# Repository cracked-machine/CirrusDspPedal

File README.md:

CirrusDspPedal

Required Kicad Hardware library: https://github.com/cracked-machine/KicadLibrary

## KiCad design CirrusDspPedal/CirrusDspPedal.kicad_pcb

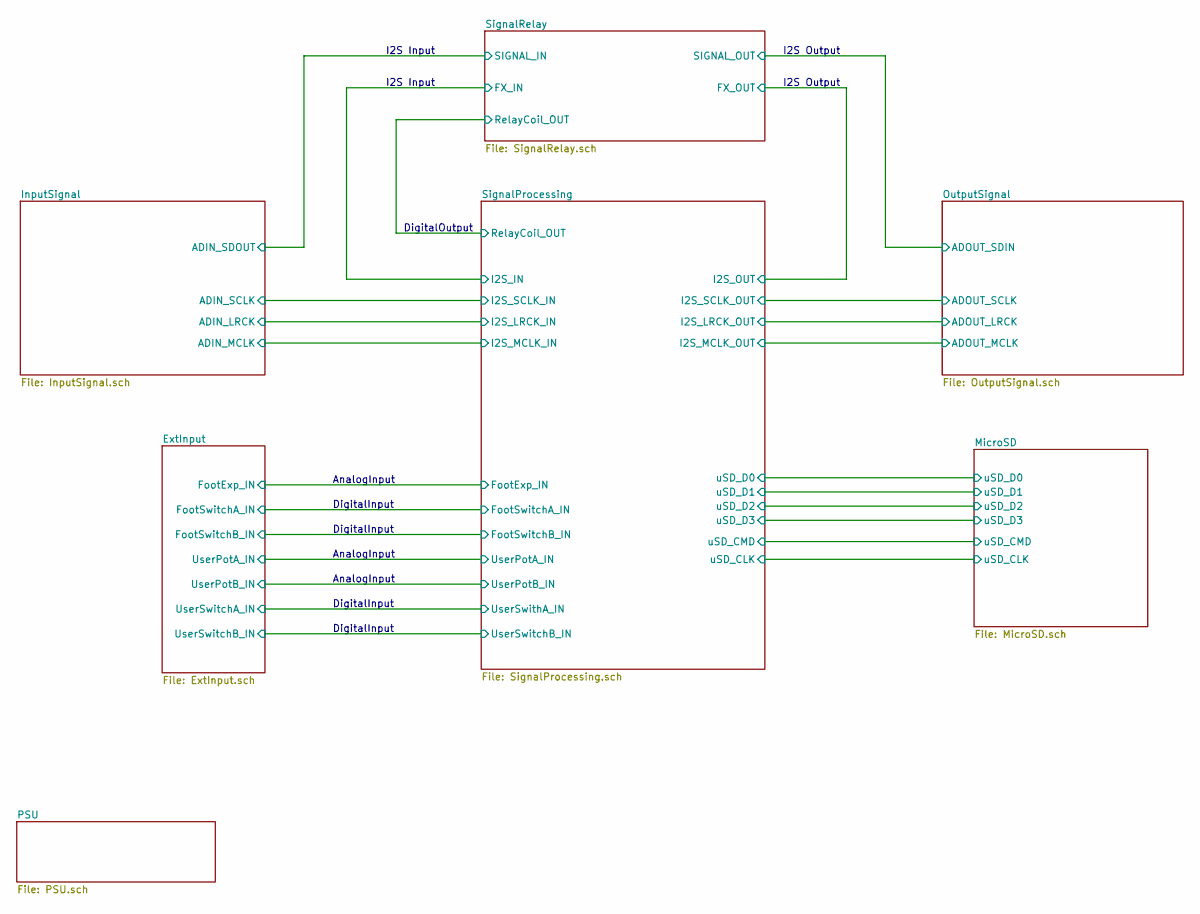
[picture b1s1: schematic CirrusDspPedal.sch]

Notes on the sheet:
AnalogInput
DigitalInput
DigitalOutput
I2S Input
I2S Output

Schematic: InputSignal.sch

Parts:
C1, C6: 100nF; C_0805_2012Metric_Pad1.15x1.40mm_HandSolder
C2, C4: 1uF; C_0805_2012Metric_Pad1.15x1.40mm_HandSolder
C3: 10uF; C_0805_2012Metric_Pad1.15x1.40mm_HandSolder
C5: 180pF C0G; C_0805_2012Metric_Pad1.15x1.40mm_HandSolder
C25, C26, C32: 1uF; C_0805_2012Metric_Pad1.18x1.45mm_HandSolder
C27, C34, C35: 100nF; C_0805_2012Metric_Pad1.18x1.45mm_HandSolder
C31: 270pF; C_0805_2012Metric_Pad1.18x1.45mm_HandSolder
D3: LED; LED_0805_2012Metric_Pad1.15x1.40mm_HandSolder
J1: MonoJack2Switch; NRJxHx_NOTAB
R1, R2: 5K1; R_0805_2012Metric_Pad1.15x1.40mm_HandSolder
R3: 10K; R_0805_2012Metric_Pad1.15x1.40mm_HandSolder
R13: 2K2; R_0805_2012Metric_Pad1.20x1.40mm_HandSolder
R14: 47R; R_0805_2012Metric_Pad1.20x1.40mm_HandSolder
R30: 100K; R_0805_2012Metric_Pad1.20x1.40mm_HandSolder
RV1: 100K; Potentiometer_Bourns_3314J_Vertical
U1: CS5343; TSSOP-10_3x3mm_P0.5mm
U2: 74AHC1G126; SOT-23-5_HandSoldering
U8: TPS60400; SOT-23-5_HandSoldering
U9: OPA197IDBV; SOT-23-5

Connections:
/InputSignal/ADIN_LRCK: U1.3 (LRCK); also elsewhere on the board
/InputSignal/ADIN_MCLK: U1.4 (MCLK); also elsewhere on the board
/InputSignal/ADIN_SCLK: U1.2 (SCLK); also elsewhere on the board
/InputSignal/ADIN_SDOUT: R3.1, U2.4; also elsewhere on the board
/InputSignal/FILT: C3.1, U1.5 (FILT)
/InputSignal/SDOUT: U1.1 (SDOUT), U2.2
/InputSignal/VA: U1.10 (VA); also elsewhere on the board
/InputSignal/VQ: C1.1, C2.1, U1.7 (VQ)
unnamed: C4.1, C5.2, U1.6 (AINL)
unnamed: C4.2, R1.1, R2.2
unnamed: C25.1, U8.3 (CFLY-)
unnamed: C25.2, U8.5 (CFLY+)
unnamed: C26.1, D3.1, R14.2, U8.1 (OUT)
unnamed: D3.2, R13.2
unnamed: J1.1 (TIP), U9.3 (+)

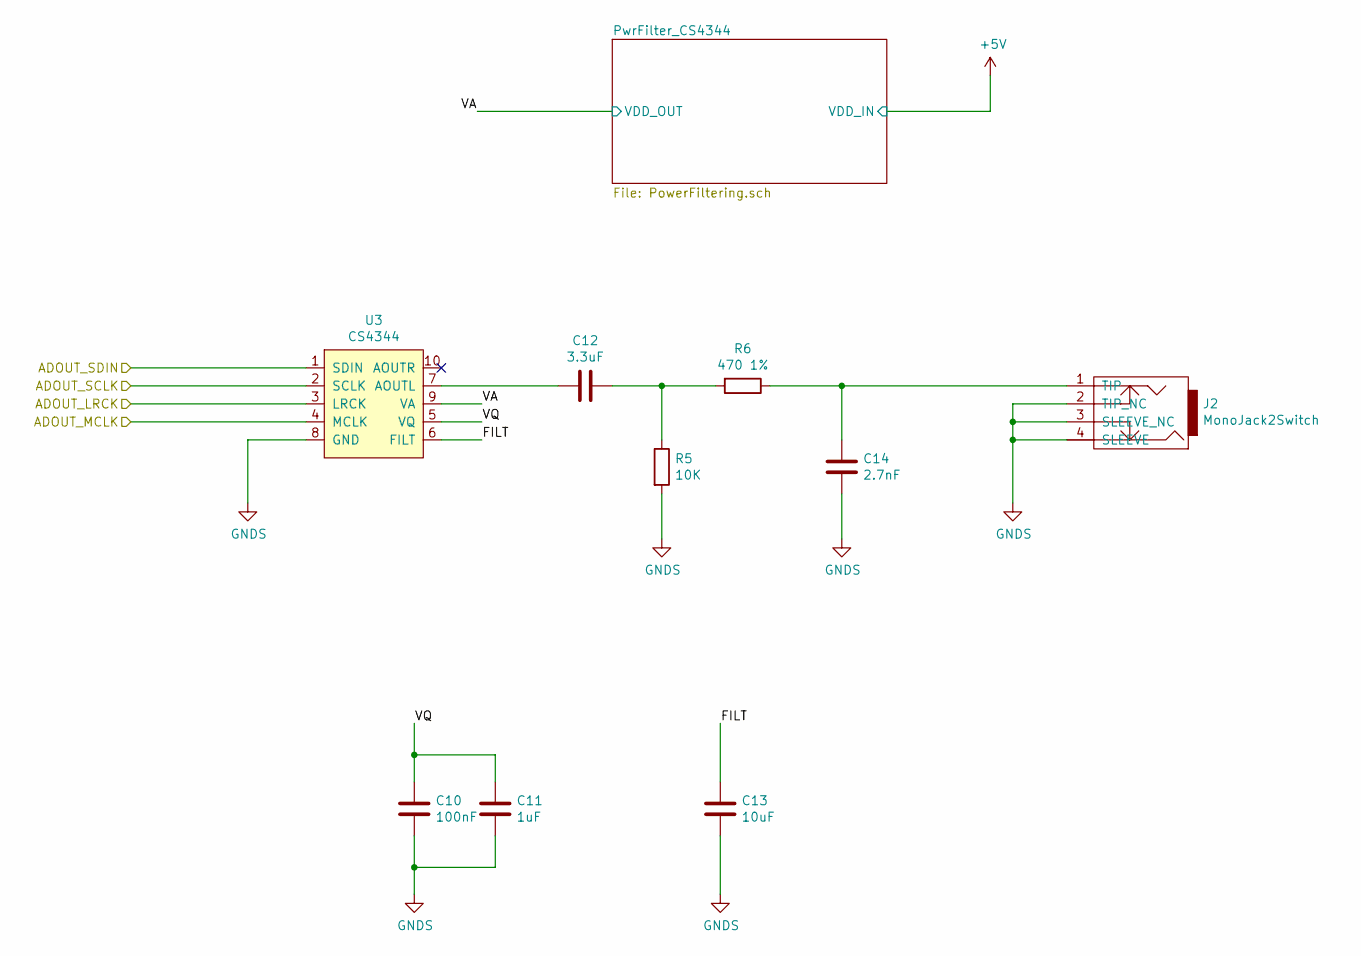
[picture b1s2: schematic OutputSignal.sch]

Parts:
C10: 100nF; C_0805_2012Metric_Pad1.15x1.40mm_HandSolder
C11: 1uF; C_0805_2012Metric_Pad1.15x1.40mm_HandSolder
C12: 3.3uF; C_0805_2012Metric_Pad1.15x1.40mm_HandSolder
C13: 10uF; C_0805_2012Metric_Pad1.15x1.40mm_HandSolder
C14: 2.7nF; C_0805_2012Metric_Pad1.15x1.40mm_HandSolder
J2: MonoJack2Switch; NRJxHx_NOTAB
R5: 10K; R_0805_2012Metric_Pad1.15x1.40mm_HandSolder
R6: 470 1%; R_0805_2012Metric_Pad1.15x1.40mm_HandSolder
U3: CS4344; TSSOP-10_3x3mm_P0.5mm

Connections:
/InputSignal/ADIN_LRCK: U3.3 (LRCK); also elsewhere on the board
/InputSignal/ADIN_MCLK: U3.4 (MCLK); also elsewhere on the board
/InputSignal/ADIN_SCLK: U3.2 (SCLK); also elsewhere on the board
/OutputSignal/ADOUT_SDIN: U3.1 (SDIN); also elsewhere on the board
/OutputSignal/FILT: C13.1, U3.6 (FILT)
/OutputSignal/VA: U3.9 (VA); also elsewhere on the board
/OutputSignal/VQ: C10.1, C11.1, U3.5 (VQ)
unnamed: C12.1, R5.1, R6.2
unnamed: C12.2, U3.7 (AOUTL)
unnamed: C14.2, J2.1 (TIP), R6.1

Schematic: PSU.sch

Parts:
C23, C24, C28, C29: 1uF; C_1206_3216Metric_Pad1.42x1.75mm_HandSolder
D1: D_Schottky; D_SOD-123F
J4: Barrel_Jack_Switch; BarrelJack_Horizontal
J7: Conn_01x01; TestPoint_Pad_2.0x2.0mm
U4: SE8250X2_SOT23; SOT-23
U5: MCP1703A-1202_SOT223; SOT-223-3_TabPin2

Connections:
+3V3: C29.1, U5.3 (VO); also elsewhere on the board
GNDPWR: J7.1; also elsewhere on the board
unnamed: C23.1, C28.1, D1.1 (K), U4.3, U5.1 (VI)
unnamed: D1.2 (A), J4.2

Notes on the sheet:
Center Negative!
16Vin Max 250mA out
30Vin Max 100mA out

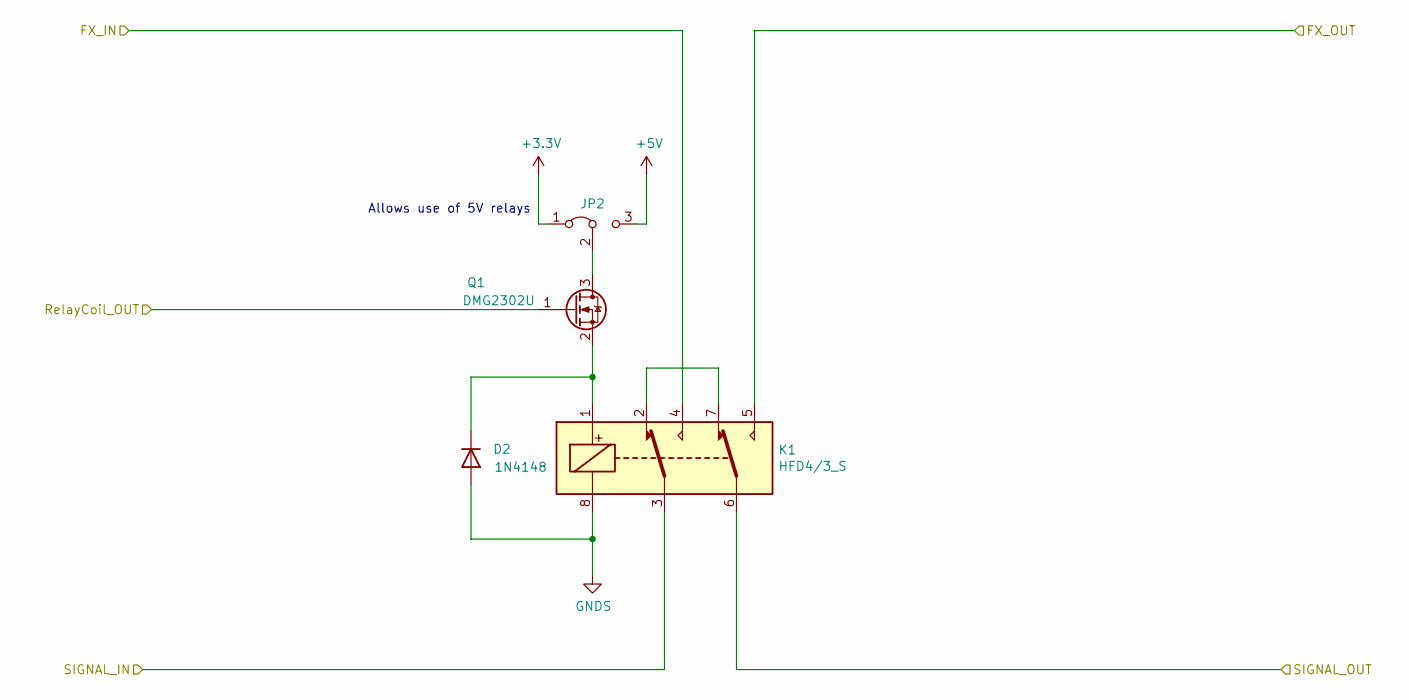
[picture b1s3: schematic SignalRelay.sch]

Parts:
D2: 1N4148; D_SOD-123F
JP2: Jumper_3_Bridged12; SolderJumper-3_P1.3mm_Bridged2Bar12_Pad1.0x1.5mm
K1: HFD4/3_S; Relay_Fujitsu_FTR-B3S
Q1: DMG2302U; SOT-23

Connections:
+3V3: JP2.1 (A); also elsewhere on the board
/InputSignal/ADIN_SDOUT: K1.3; also elsewhere on the board
/OutputSignal/ADOUT_SDIN: K1.6; also elsewhere on the board
/SignalProcessing/RelayCoil_OUT: Q1.1 (G); also elsewhere on the board
/SignalRelay/FX_IN: K1.4; also elsewhere on the board
/SignalRelay/FX_OUT: K1.5; also elsewhere on the board
unnamed: D2.1 (K), K1.1, Q1.2 (S)
unnamed: JP2.2 (C), Q1.3 (D)
unnamed: K1.2, K1.7

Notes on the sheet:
Allows use of 5V relays

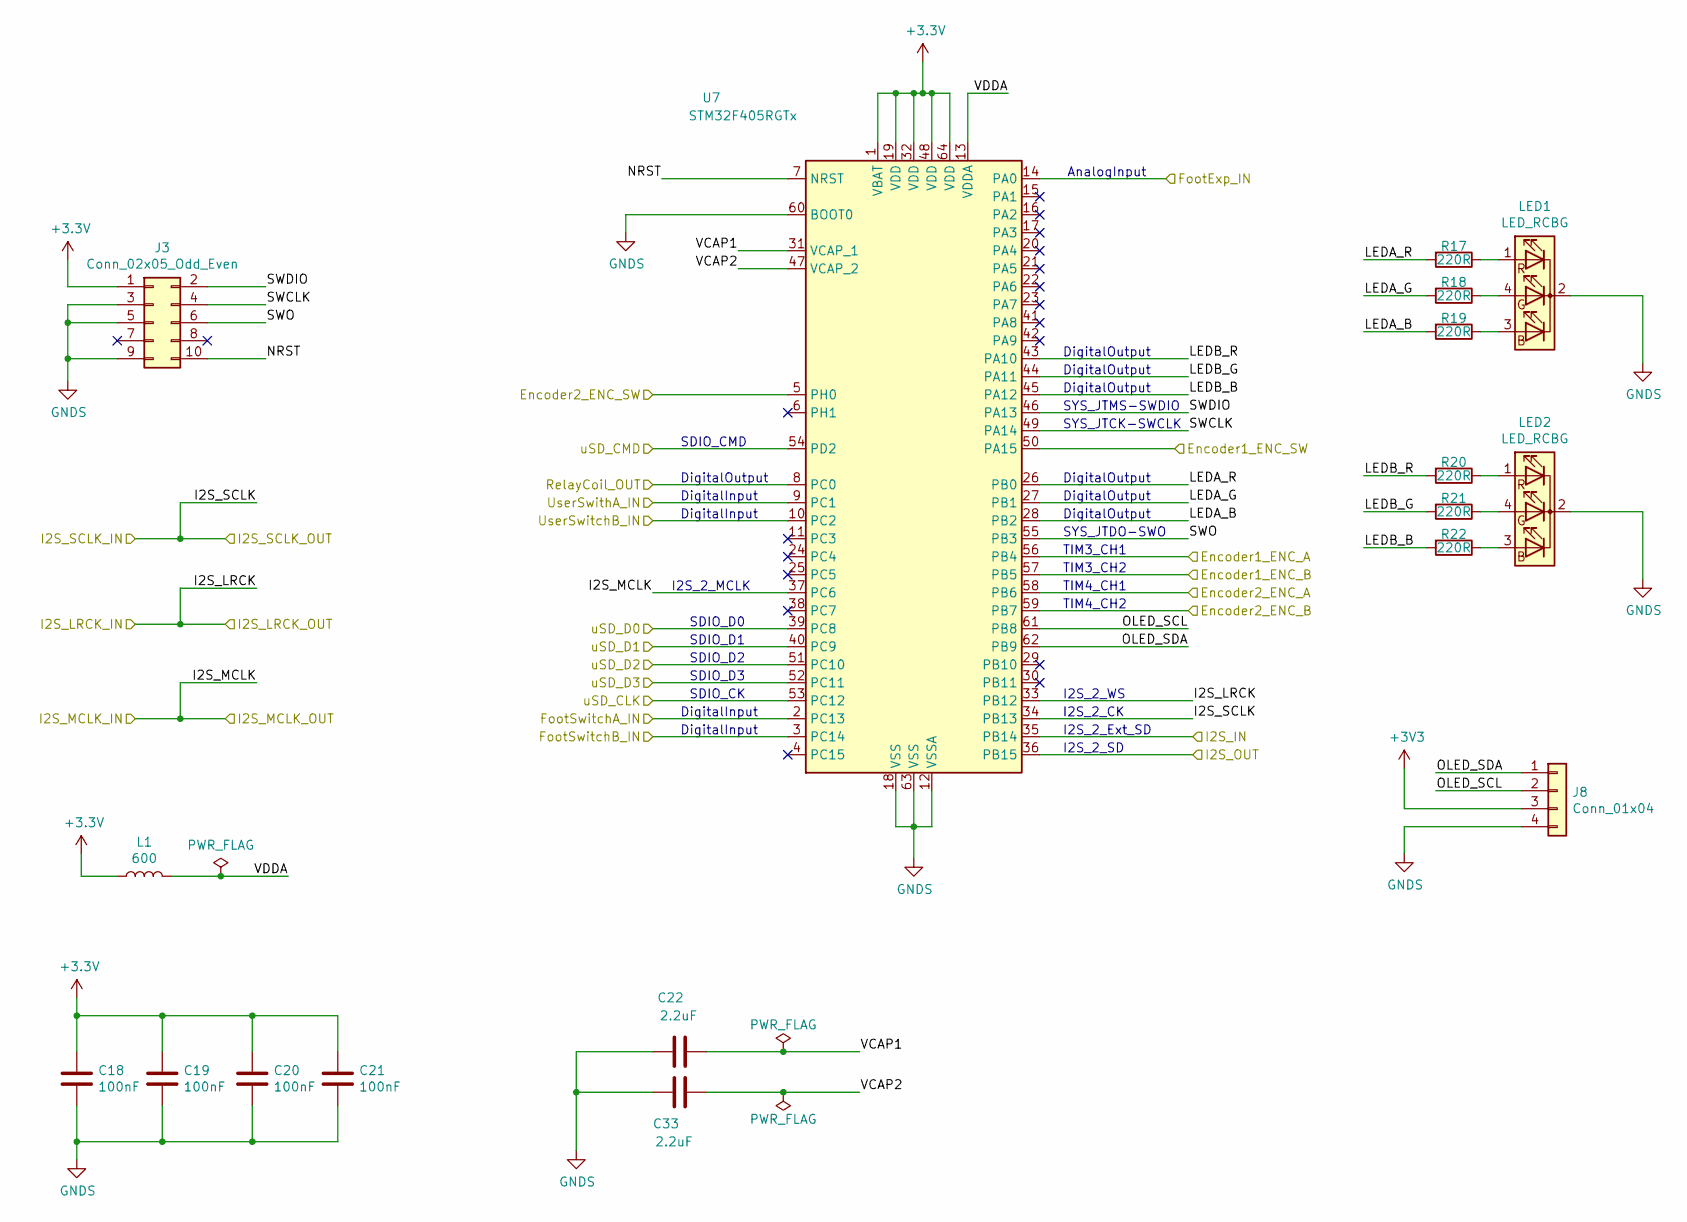
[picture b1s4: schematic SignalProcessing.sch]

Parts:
C18, C19, C20, C21: 100nF; C_0805_2012Metric_Pad1.15x1.40mm_HandSolder
C22, C33: 2.2uF; C_0805_2012Metric_Pad1.15x1.40mm_HandSolder
J3: Conn_02x05_Odd_Even; PinHeader_2x05_P1.27mm_Vertical_SMD
J8: Conn_01x04; Molex_KK-254_AE-6410-04A_1x04_P2.54mm_Vertical
L1: 600; L_0805_2012Metric_Pad1.15x1.40mm_HandSolder
LED1, LED2: LED_RCBG; LED_D5.0mm-4_RGB_Wide_Pins
R17, R18, R19, R20, R21, R22: 220R; R_0805_2012Metric_Pad1.15x1.40mm_HandSolder
U7: STM32F405RGTx; LQFP-64_10x10mm_P0.5mm

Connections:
+3V3: C18.1, C19.1, C20.1, C21.1, J3.1, L1.1, U7.1 (VBAT), U7.19 (VDD), U7.32 (VDD), U7.48 (VDD), U7.64 (VDD); also elsewhere on the board
/ExtInput/Encoder1_ENC_A: U7.56 (PB4); also elsewhere on the board
/ExtInput/Encoder1_ENC_B: U7.57 (PB5); also elsewhere on the board
/ExtInput/Encoder1_ENC_SW: U7.50 (PA15); also elsewhere on the board
/ExtInput/Encoder2_ENC_SW: U7.5 (PH0); also elsewhere on the board
/ExtInput/FootExp_IN: U7.14 (PA0); also elsewhere on the board
/ExtInput/FootSwitchA_IN: U7.2 (PC13); also elsewhere on the board
/ExtInput/FootSwitchB_IN: U7.3 (PC14); also elsewhere on the board
/ExtInput/UserSwitchA_IN: U7.9 (PC1); also elsewhere on the board
/ExtInput/UserSwitchB_IN: U7.10 (PC2); also elsewhere on the board
/InputSignal/ADIN_LRCK: U7.33 (PB12); also elsewhere on the board
/InputSignal/ADIN_MCLK: U7.37 (PC6); also elsewhere on the board
/InputSignal/ADIN_SCLK: U7.34 (PB13); also elsewhere on the board
/MicroSD/uSD_CLK: U7.53 (PC12); also elsewhere on the board
/MicroSD/uSD_CMD: U7.54 (PD2); also elsewhere on the board
/MicroSD/uSD_D0: U7.39 (PC8); also elsewhere on the board
/MicroSD/uSD_D1: U7.40 (PC9); also elsewhere on the board
/MicroSD/uSD_D2: U7.51 (PC10); also elsewhere on the board
/MicroSD/uSD_D3: U7.52 (PC11); also elsewhere on the board
/SignalProcessing/LEDA_B: R19.2, U7.28 (PB2)
/SignalProcessing/LEDA_G: R18.2, U7.27 (PB1)
/SignalProcessing/LEDA_R: R17.2, U7.26 (PB0)
/SignalProcessing/LEDB_B: R22.2, U7.45 (PA12)
/SignalProcessing/LEDB_G: R21.2, U7.44 (PA11)
/SignalProcessing/LEDB_R: R20.2, U7.43 (PA10)
/SignalProcessing/NRST: J3.10, U7.7 (NRST)
/SignalProcessing/OLED_SCL: J8.2, U7.61 (PB8)
/SignalProcessing/OLED_SDA: J8.1, U7.62 (PB9)
/SignalProcessing/RelayCoil_OUT: U7.8 (PC0); also elsewhere on the board
/SignalProcessing/SWCLK: J3.4, U7.49 (PA14)
/SignalProcessing/SWDIO: J3.2, U7.46 (PA13)
/SignalProcessing/SWO: J3.6, U7.55 (PB3)
/SignalProcessing/VCAP1: C22.2, U7.31 (VCAP_1)
/SignalProcessing/VCAP2: C33.2, U7.47 (VCAP_2)
/SignalProcessing/VDDA: L1.2, U7.13 (VDDA)
/SignalRelay/FX_IN: U7.35 (PB14); also elsewhere on the board
/SignalRelay/FX_OUT: U7.36 (PB15); also elsewhere on the board
unnamed 67: J8.3; also elsewhere on the board
unnamed: LED1.1 (RA), R17.1
unnamed: LED1.3 (BA), R19.1
unnamed: LED1.4 (GA), R18.1
unnamed: LED2.1 (RA), R20.1
unnamed: LED2.3 (BA), R22.1
unnamed: LED2.4 (GA), R21.1

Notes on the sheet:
I2S_2_CK
I2S_2_MCLK
I2S_2_WS
I2S_2_Ext_SD
I2S_2_SD
DigitalOutput
DigitalInput
AnalogInput
SYS_JTDO-SWO
SYS_JTMS-SWDIO
SYS_JTCK-SWCLK
SDIO_D0
SDIO_D1
SDIO_D2
SDIO_D3
SDIO_CK
SDIO_CMD
TIM3_CH1
TIM3_CH2
TIM4_CH1
TIM4_CH2

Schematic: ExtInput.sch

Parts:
C30, C31, C32: 100nF; C_0805_2012Metric_Pad1.15x1.40mm_HandSolder
J5: MonoJack2Switch; NRJxHx_NOTAB
R8, R13, R14: 50R; R_0805_2012Metric_Pad1.15x1.40mm_HandSolder
R9, R10, R15, R16: 1K; R_0805_2012Metric_Pad1.15x1.40mm_HandSolder
R11, R12: 100R; R_0805_2012Metric_Pad1.15x1.40mm_HandSolder
RV1, RV2: RK09L1140A65; Potentiometer_Alps_RK09L_Single_Vertical
SW1, SW2: P26L-1D-RND MTL; PinSocket_1x02_P2.54mm_Vertical
SW3, SW4: SW_SPST; SW_SPDT_W6.86MM_L12.7MM_P4.8MM_D2MM
U6: MCP601-xOT; SOT-23-5

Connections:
+3V3: R9.1, R10.1, R11.1, R12.1, R15.1, R16.1, U6.5 (V+); also elsewhere on the board
/ExtInput/FootExp_IN: C30.2, R8.1; also elsewhere on the board
/ExtInput/FootSwitchA_IN: R9.2, SW1.2 (B); also elsewhere on the board
/ExtInput/FootSwitchB_IN: R10.2, SW2.2 (B); also elsewhere on the board
/ExtInput/UserSwitchA_IN: R15.2, SW3.2 (B); also elsewhere on the board
/ExtInput/UserSwitchB_IN: R16.2, SW4.2 (B); also elsewhere on the board
unnamed 57: R14.2; also elsewhere on the board
unnamed 60: R13.2; also elsewhere on the board
unnamed: J5.1 (TIP), U6.3 (+)
unnamed: R8.2, U6.1, U6.4 (-)

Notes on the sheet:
Use RK09D1130A1N is longer shaft required

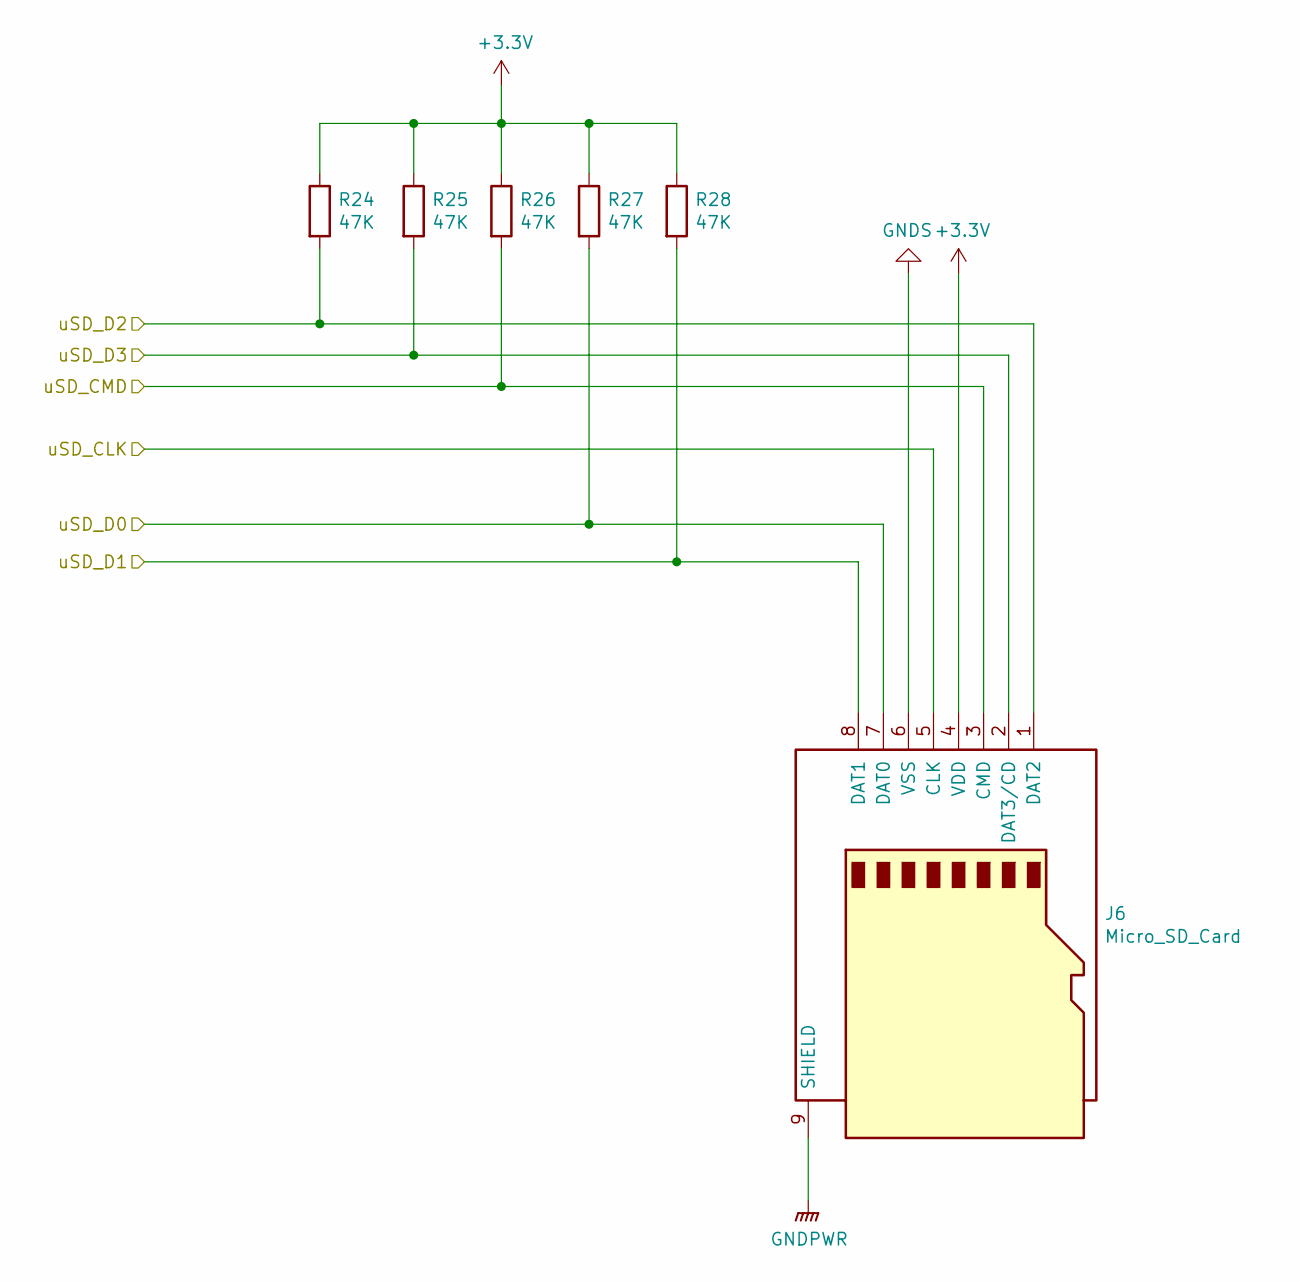
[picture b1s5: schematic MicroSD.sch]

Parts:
J6: Micro_SD_Card; Molex_SDIO_475710001
R24, R25, R26, R27, R28: 47K; R_0805_2012Metric_Pad1.15x1.40mm_HandSolder

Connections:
+3V3: J6.4 (VDD), R24.1, R25.1, R26.1, R27.1, R28.1; also elsewhere on the board
/MicroSD/uSD_CLK: J6.5 (CLK); also elsewhere on the board
/MicroSD/uSD_CMD: J6.3 (CMD), R26.2; also elsewhere on the board
/MicroSD/uSD_D0: J6.7 (DAT0), R27.2; also elsewhere on the board
/MicroSD/uSD_D1: J6.8 (DAT1), R28.2; also elsewhere on the board
/MicroSD/uSD_D2: J6.1 (DAT2), R24.2; also elsewhere on the board
/MicroSD/uSD_D3: J6.2 (DAT3/CD), R25.2; also elsewhere on the board
GNDPWR: J6.9 (SHIELD); also elsewhere on the board

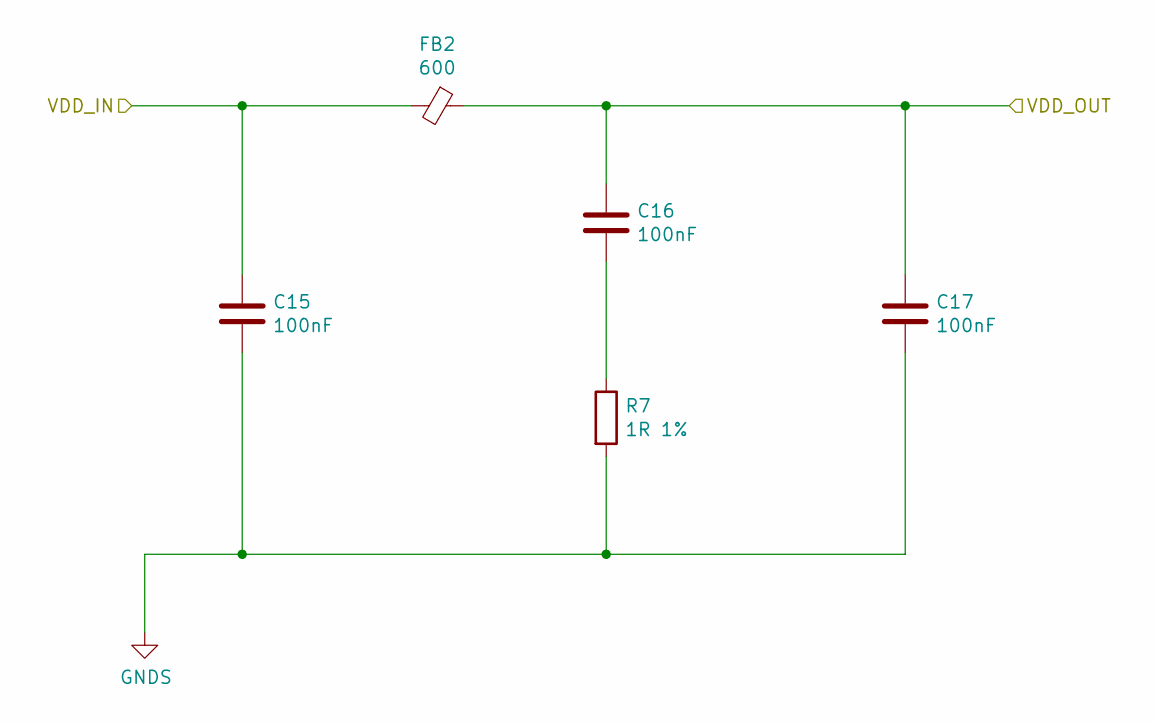
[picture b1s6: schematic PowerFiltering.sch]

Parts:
C7, C8, C9: 100nF; C_0805_2012Metric_Pad1.15x1.40mm_HandSolder
FB1: 600; L_0805_2012Metric_Pad1.15x1.40mm_HandSolder
R4: 1R 1%; R_0805_2012Metric_Pad1.15x1.40mm_HandSolder

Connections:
/InputSignal/VA: C8.1, C9.1, FB1.1; also elsewhere on the board
unnamed: C8.2, R4.1

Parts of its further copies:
C15, C16, C17: 100nF; C_0805_2012Metric_Pad1.15x1.40mm_HandSolder
FB2: 600; L_0805_2012Metric_Pad1.15x1.40mm_HandSolder
R7: 1R 1%; R_0805_2012Metric_Pad1.15x1.40mm_HandSolder

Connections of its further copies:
/OutputSignal/VA: C16.1, C17.1, FB2.1; also elsewhere on the board
unnamed: C16.2, R7.1

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
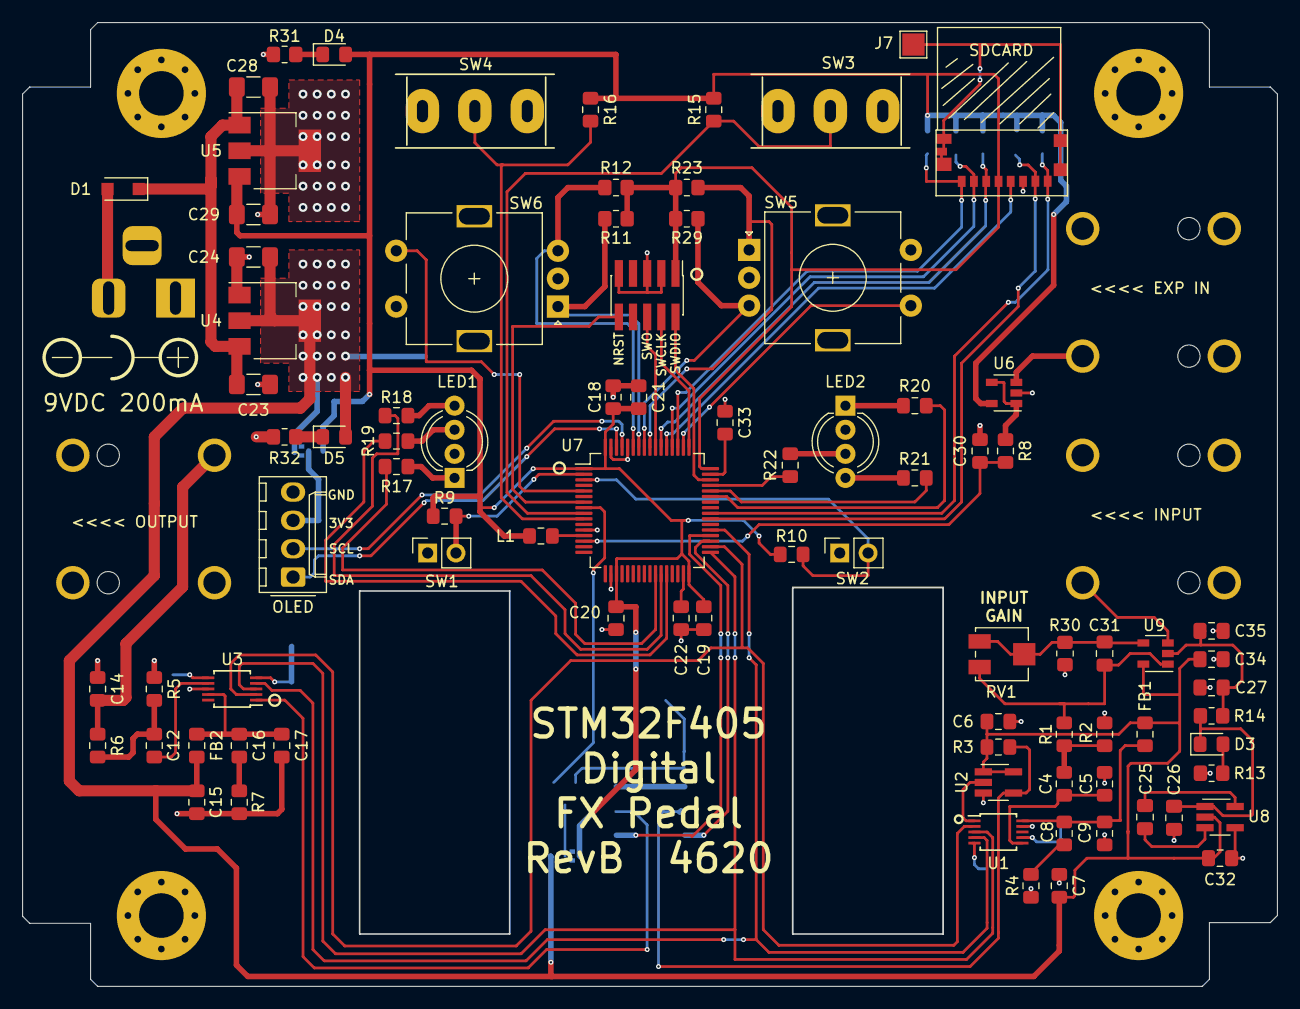
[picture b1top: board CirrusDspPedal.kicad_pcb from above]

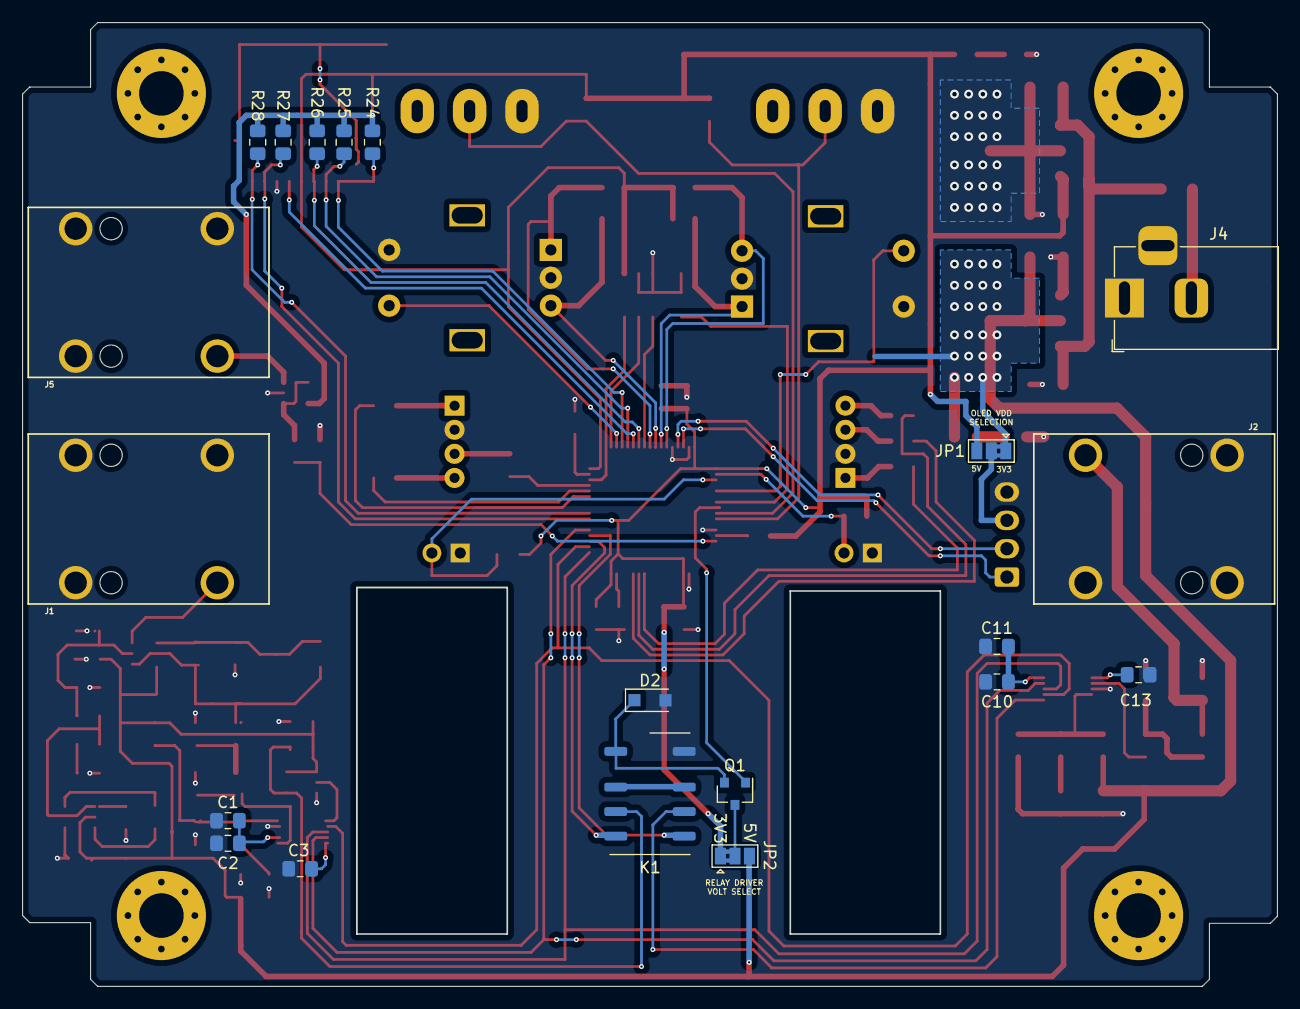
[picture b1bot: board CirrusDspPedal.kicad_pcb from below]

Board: 2 copper layers, 112.5 x 86.4 mm, 105 parts (20 on the bottom side), 82 nets.

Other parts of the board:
D4, D5: LED; LED_0805_2012Metric_Pad1.15x1.40mm_HandSolder
JP1: Jumper_3_Bridged12; SolderJumper-3_P1.3mm_Bridged2Bar12_Pad1.0x1.5mm
R23, R29: 10K; R_0805_2012Metric_Pad1.20x1.40mm_HandSolder
R31, R32: 2K2; R_0805_2012Metric_Pad1.20x1.40mm_HandSolder
SW5, SW6: PEC11R-4020K-S0024; RotaryEncoder_Alps_EC11E-Switch_Vertical_H20mm

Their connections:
+3V3: D4.2, JP1.3, R23.1, R29.1; also elsewhere on the board
/ExtInput/Encoder1_ENC_A: R23.2, SW5.A; also elsewhere on the board
/ExtInput/Encoder1_ENC_B: R29.2, SW5.B; also elsewhere on the board
/ExtInput/Encoder1_ENC_SW: SW5.S1; also elsewhere on the board
/ExtInput/Encoder2_ENC_SW: SW6.S1; also elsewhere on the board
unnamed: D4.1, R31.2
unnamed: D5.1, R32.2
unnamed 67: JP1.2; also elsewhere on the board

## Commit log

2020-10-11 first draft schema design
2020-10-12 Added Footswitches and relay
2020-10-12 updated schema docs
2020-10-18 Added UserPots and RGB LEDS
    Updated schema docs
2020-10-18 Completed schematic design
2020-10-19 finished RevA layout
2020-10-29 updated design and layout
    - Changed LDO to 1703 (footprint unchanged)
    - Changed THT LEDs from RAGB (incorrect) to RCGB (correct) symbol (footprint unchanged)
2020-10-29 updated design and layout
    - Changed LDO package from SOT23 to SOT223
2020-10-31 Updated design
    - Corrected trace going to wrong CS4344 channel output
2020-11-06 finished revb layout
2020-11-07 updated revb
    - Added n-chan and 5V/3V3 jumper for relay
    - Moved MCU to the middle of PCB (more space)
2020-11-07 updated gerbers/schematic docs
2020-11-08 replaced SDIO connector
2020-11-10 Updated RevB
    - Replaced analog pots with Rotary Encoders
    - Added I2C connector (for OLED screen)
2020-11-10 updated revB
    - Added higher out current LDO (LD1117) for 5V rail
    - Added jumper on OLED connector to select 3V3/5V
2020-11-10 updated revb
    - Added input amp with charge pump and protection diodes
2020-11-12 updated revb
    - Moved THT components to improve UX layout
2020-11-12 final revb layout
2020-11-28 Added second project for front panel: "CirrusDspPedal_FrontPanel"
    No components or traces, edge cuts, silkscreen and top copper pour only
2021-01-09 modified front panel
    Raised footswitch holes by 3mm
2021-06-18 Create LICENSE
